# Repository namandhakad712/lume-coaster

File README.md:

### lume-coaster

This project is mostly different but similar to other projects, everyone is using the the hardware suggested and the utitlities in the starter guide of [Starbie](https://github.com/SharKingStudios/Starbie) project.
But lmao people forgot that that 's [guide link](https://github.com/SharKingStudios/Starbie/blob/main/Week%201%20Guide.md), a beginner path to creativity not limit to it.

###### what is made
A carrier board (sandwitch)🥪 for the Tuya **T5AI-Core** ([Link](https://tuyaopen.ai/docs/hardware/tuya-t5/t5-ai-core/overview-t5-ai-core)) module — the kind of board, might be thinking what it is , it is a better much development board than ESP32 one's.
you design once so the module stops being a tangle of Dupont wires and starts
being an actual thing on your desk. It's a coaster-sized slab that the module
plugs into.

## See the layering system:

```
________________________________________
          tft-screen[__] | buttons (o) 
________________________________________
          Our Lume sandwitch board
__|_|_|_|_|_|_|_|_|_|_|_|_|_|_|_|_|_|_|_
         The T5 AI Core board
________________________________________

```

Some text here , if my visual was little out of understandabe scope 🥲

It breaks the module out onto a single 85 × 40 mm PCB:

- a 44-pin socket for the module,

OR 

```
+-----------------------------------+
|  [::] [::] [::] [::] [::] [::]    |  <-- Pin Rows 1 to 22
|                                   |
|       ( MAIN TARGET MODULE )      |
|                                   |
|  [::] [::] [::] [::] [::] [::]    |  <-- Pin Rows 23 to 44
+-----------------------------------+
          |||||||||||||||
```
- a 9-pin header for a 2.8" **ILI9341** SPI colour LCD ,

- **Three tactile buttons** (mode / up / down),
```
     +------------+------------+
     |            |            |
     v            v            v
  +-----+      +-----+      +-----+
  |     |      |     |      |     |
  |MODE |      | UP  |      |DOWN |
  |     |      |     |      |     |
  +-----+      +-----+      +-----+
  (Tactile)    (Tactile)    (Tactile)
```
- a 3-pin header for an active chime / buzzer,
- an onboard **single-cell LiPo battery supply** with a USB-C charge path,

- a P-MOS high-side switch for the display backlight.

It's a board, on its own, that does a job. Power it from USB-C or a LiPo,
plug in a display, and it shows whatever the module is running.

# Why this board

Basically, i already have it,😗 so instead of buying a new development board, I used it.
The T5AI-Core is a module, not a dev-kit. To use it for anything you either, its has mic, speaker, ASR built-in and much more.
hand-wire a breakout every single time, or you design one carrier board once
and never think about it again. This is the second one.

Everything on it is chosen to be unremarkable and reliable:
- [x] Has own USB-Type C port
- [x] Has own 5V-3.3Volt Power management
- [x] Has it own built-in ASR
- [x] On device 16MB RAM
- [x] Optimized for battery based edge cases
- [x] Integrated 2.4 GHz Wi-Fi and Bluetooth low energy (LE) 5.4

## Repo layout

```
carrier-board/      all board contents - netlist, pin map, schematic notes, layout constraints
reference/          module pinout screenshots used while pinning out J1
kicad-noob-guide.md [FOR BEGINNERS] the build procedure, block by block 
BOM.md              parts list
JOURNAL.md          work journey log
```

## Hardware one-liner Flow

LiPo or USB-C ⇀ module's own charge path and regulators ⇀ +3V3 rail ⇀
ILI9341 over SPI0, three buttons, one chime header, one P-MOS backlight.

Full net list, per-pin reasoning, and why each pin was picked or avoided:
[`carrier-board/netlist-pinmap.md`](carrier-board/netlist-pinmap.md).

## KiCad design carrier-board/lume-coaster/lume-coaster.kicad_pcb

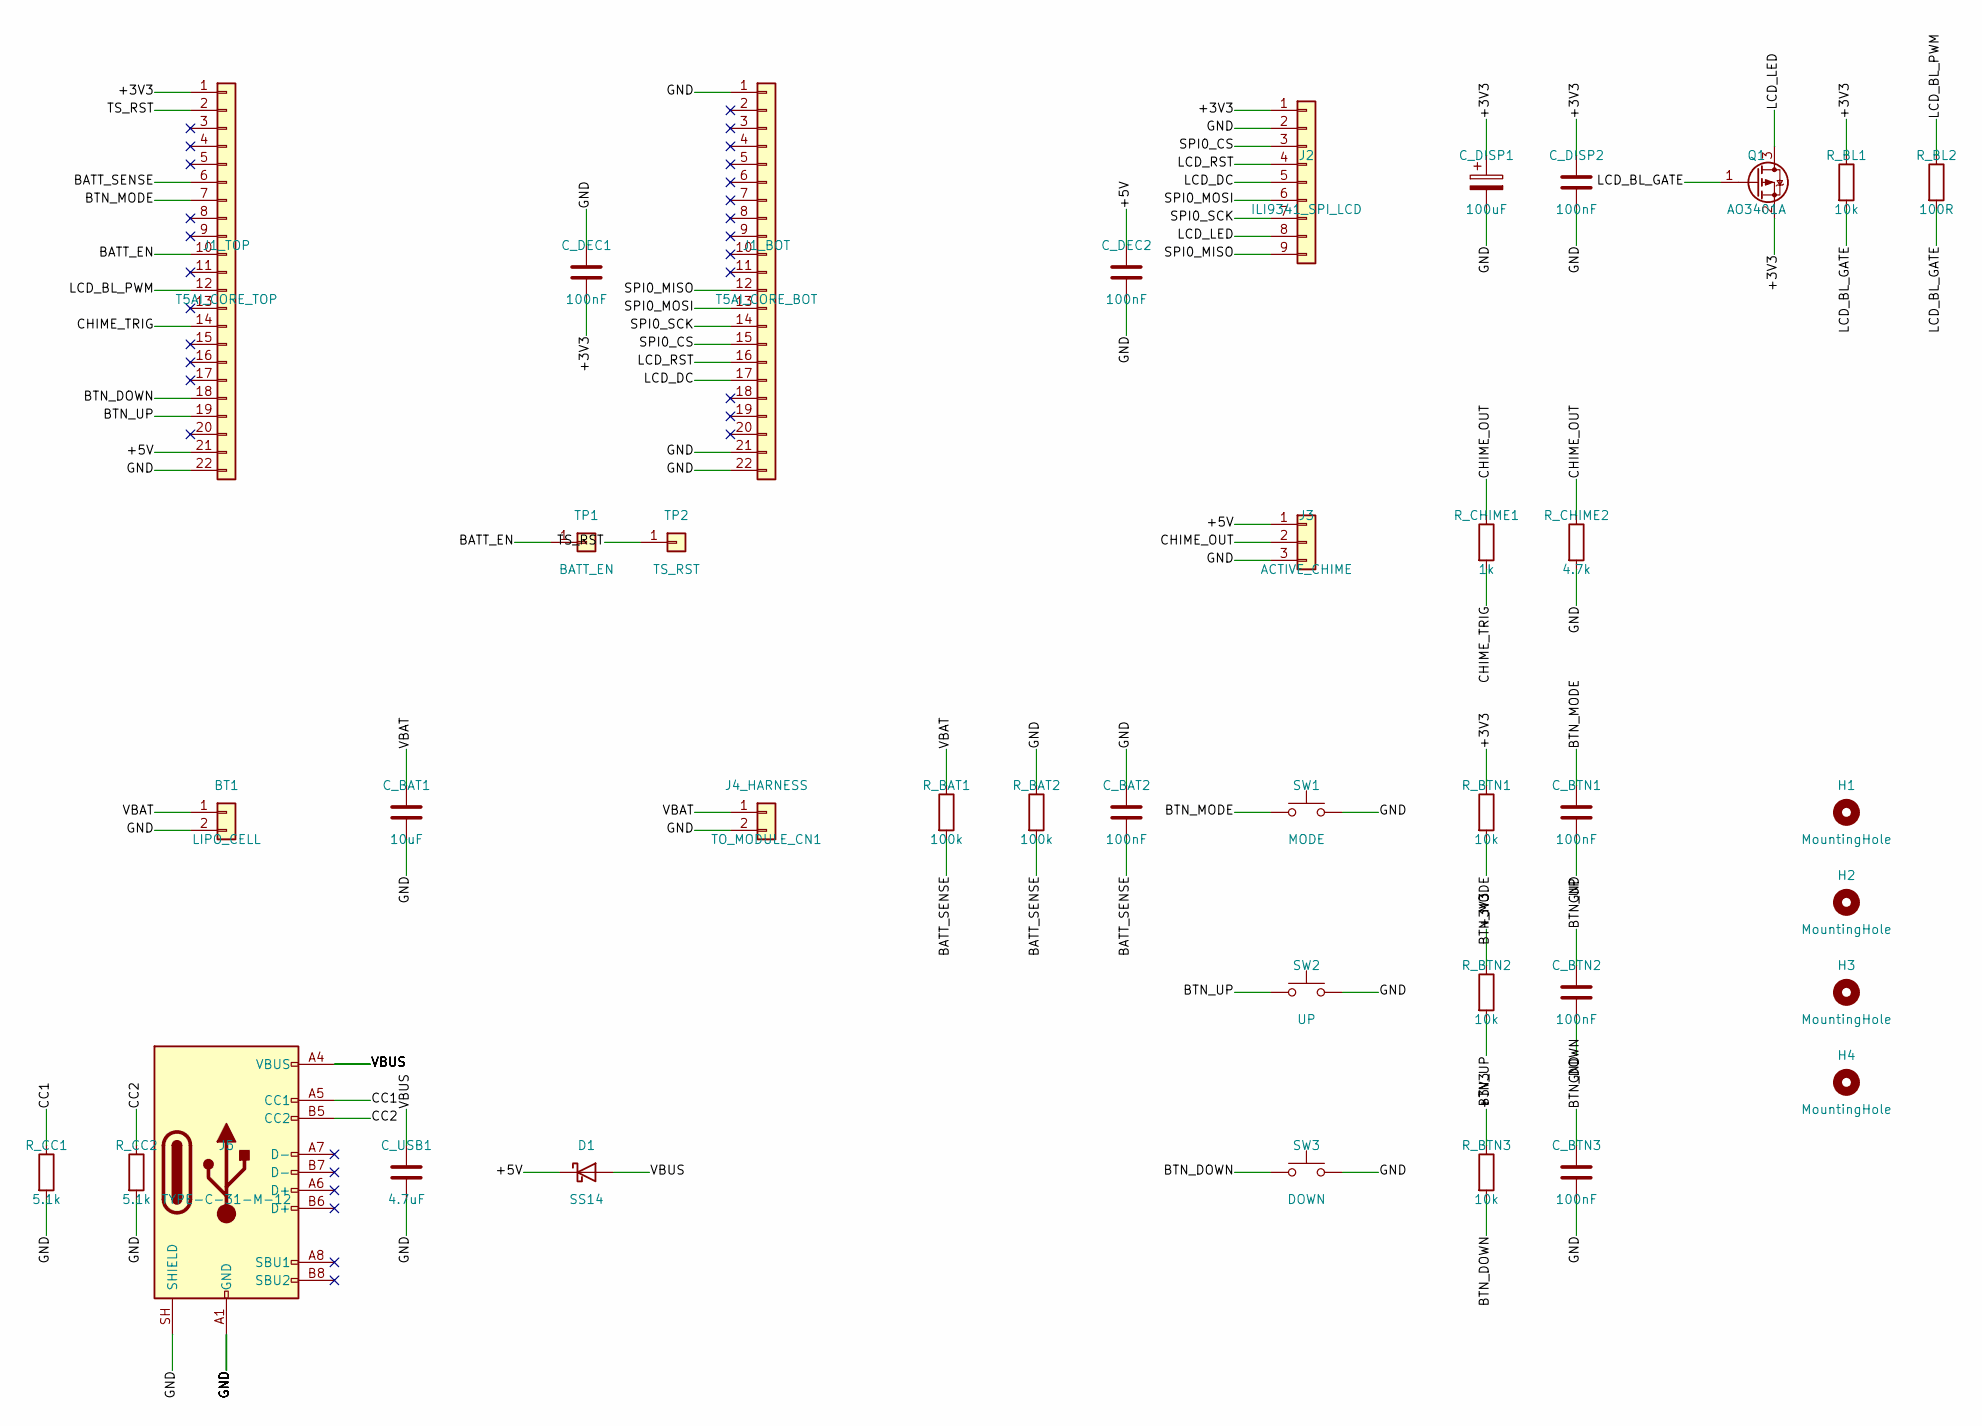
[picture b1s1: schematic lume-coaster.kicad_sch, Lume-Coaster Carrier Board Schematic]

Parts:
BT1: LIPO_CELL; JST_PH_S2B-PH-K_1x02_P2.00mm_Horizontal
C_BAT1: 10uF; C_0805_2012Metric
C_BAT2: 100nF; C_0805_2012Metric
C_BTN1, C_BTN2, C_BTN3: 100nF; C_0805_2012Metric
C_DEC1, C_DEC2: 100nF; C_0805_2012Metric
C_DISP1: 100uF; CP_Elec_6.3x5.4
C_DISP2: 100nF; C_0805_2012Metric
C_USB1: 4.7uF; C_0805_2012Metric
D1: SS14; D_SMA
H1, H2, H3, H4: MountingHole; MountingHole_3.2mm_M3
J1_BOT: T5AI_CORE_BOT; PinSocket_1x22_P2.54mm_Vertical
J1_TOP: T5AI_CORE_TOP; PinSocket_1x22_P2.54mm_Vertical
J2: ILI9341_SPI_LCD; PinHeader_1x09_P2.54mm_Vertical
J3: ACTIVE_CHIME; PinHeader_1x03_P2.54mm_Horizontal
J4_HARNESS: TO_MODULE_CN1; JST_GH_SM02B-GHS-TB_1x02-1MP_P1.25mm_Horizontal
J5: TYPE-C-31-M-12; USB_C_Receptacle_HRO_TYPE-C-31-M-12
Q1: AO3401A; SOT-23
R_BAT1, R_BAT2: 100k; R_0805_2012Metric
R_BL1: 10k; R_0805_2012Metric
R_BL2: 100R; R_0805_2012Metric
R_BTN1, R_BTN2, R_BTN3: 10k; R_0805_2012Metric
R_CC1, R_CC2: 5.1k; R_0805_2012Metric
R_CHIME1: 1k; R_0805_2012Metric
R_CHIME2: 4.7k; R_0805_2012Metric
SW1: MODE; SW_Push_1TS009xxxx-xxxx-xxxx_6x6x5mm
SW2: UP; SW_Push_1TS009xxxx-xxxx-xxxx_6x6x5mm
SW3: DOWN; SW_Push_1TS009xxxx-xxxx-xxxx_6x6x5mm
TP1: BATT_EN; TestPoint_Pad_D1.0mm
TP2: TS_RST; TestPoint_Pad_D1.0mm

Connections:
/+3V3: C_DEC1.2, C_DISP1.1, C_DISP2.1, J1_TOP.1, J2.1, Q1.2 (S), R_BL1.1, R_BTN1.1, R_BTN2.1, R_BTN3.1
/+5V: C_DEC2.1, D1.1 (K), J1_TOP.21, J3.1
/BATT_EN: J1_TOP.10, TP1.1
/BATT_SENSE: C_BAT2.2, J1_TOP.6, R_BAT1.2, R_BAT2.2
/BTN_DOWN: C_BTN3.1, J1_TOP.18, R_BTN3.2, SW3.1
/BTN_MODE: C_BTN1.1, J1_TOP.7, R_BTN1.2, SW1.1
/BTN_UP: C_BTN2.1, J1_TOP.19, R_BTN2.2, SW2.1
/CC1: J5.A5 (CC1), R_CC1.1
/CC2: J5.B5 (CC2), R_CC2.1
/CHIME_OUT: J3.2, R_CHIME1.1, R_CHIME2.1
/CHIME_TRIG: J1_TOP.14, R_CHIME1.2
/GND: BT1.2, C_BAT1.2, C_BAT2.1, C_BTN1.2, C_BTN2.2, C_BTN3.2, C_DEC1.1, C_DEC2.2, C_DISP1.2, C_DISP2.2, C_USB1.2, J1_BOT.1, J1_BOT.21, J1_BOT.22, J1_TOP.22, J2.2, J3.3, J4_HARNESS.2, J5.A1 (GND), J5.A12 (GND), J5.B1 (GND), J5.B12 (GND), J5.SH (SHIELD), R_BAT2.1, R_CC1.2, R_CC2.2, R_CHIME2.2, SW1.2, SW2.2, SW3.2
/LCD_BL_GATE: Q1.1 (G), R_BL1.2, R_BL2.2
/LCD_BL_PWM: J1_TOP.12, R_BL2.1
/LCD_DC: J1_BOT.17, J2.5
/LCD_LED: J2.8, Q1.3 (D)
/LCD_RST: J1_BOT.16, J2.4
/SPI0_CS: J1_BOT.15, J2.3
/SPI0_MISO: J1_BOT.12, J2.9
/SPI0_MOSI: J1_BOT.13, J2.6
/SPI0_SCK: J1_BOT.14, J2.7
/TS_RST: J1_TOP.2, TP2.1
/VBAT: BT1.1, C_BAT1.1, J4_HARNESS.1, R_BAT1.1
/VBUS: C_USB1.1, D1.2 (A), J5.A4 (VBUS), J5.A9 (VBUS), J5.B4 (VBUS), J5.B9 (VBUS)

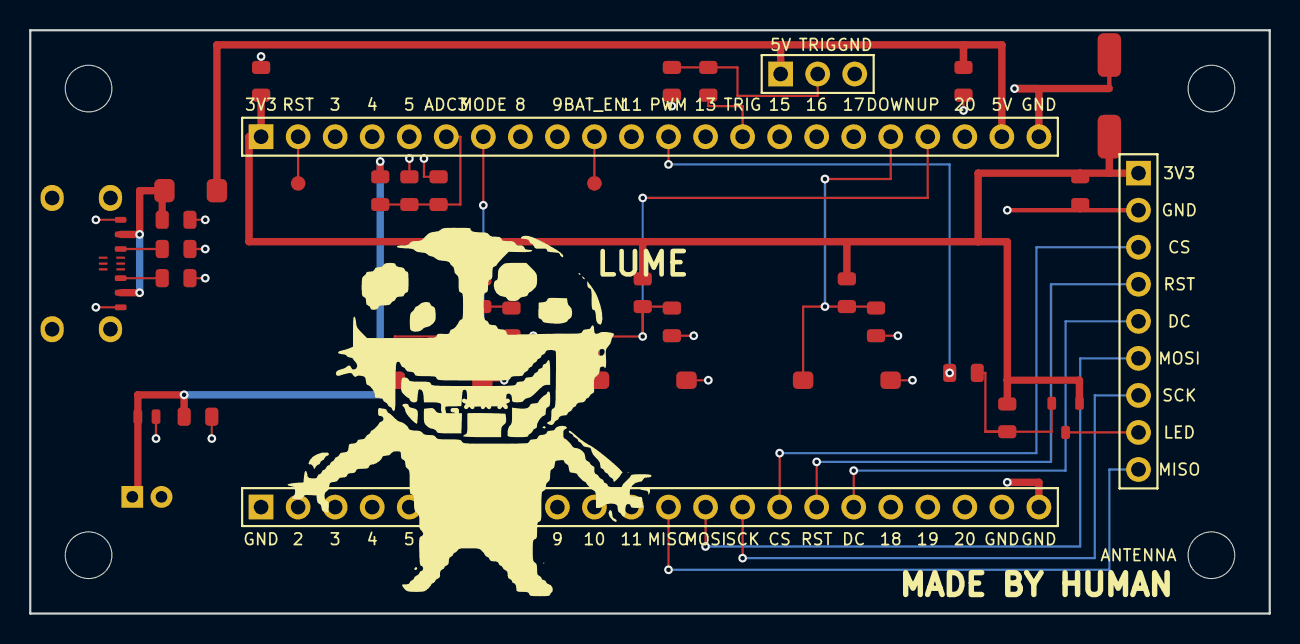
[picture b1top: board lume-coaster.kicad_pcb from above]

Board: 2 copper layers, 85.0 x 40.0 mm, 39 parts (0 on the bottom side), 24 nets.
